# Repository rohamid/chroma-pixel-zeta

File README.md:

# TODO #
* Using IS42S16160 which is actually 32MB SDRAM, there must be 13 bit address (A0-A12). But I only populated 12-bit (A0-A11). Fix This
* Move the LCD FPC 40P slightly inside the PCB in order to match the actual LCD bend.
* Add VBUS control to the USB C in order to use USB Host capability
* I forgot to route 5V to 4P the JST-XH connector
* Rotate the ST-Link connector 180 degree to match the actual ST-Link connector bend

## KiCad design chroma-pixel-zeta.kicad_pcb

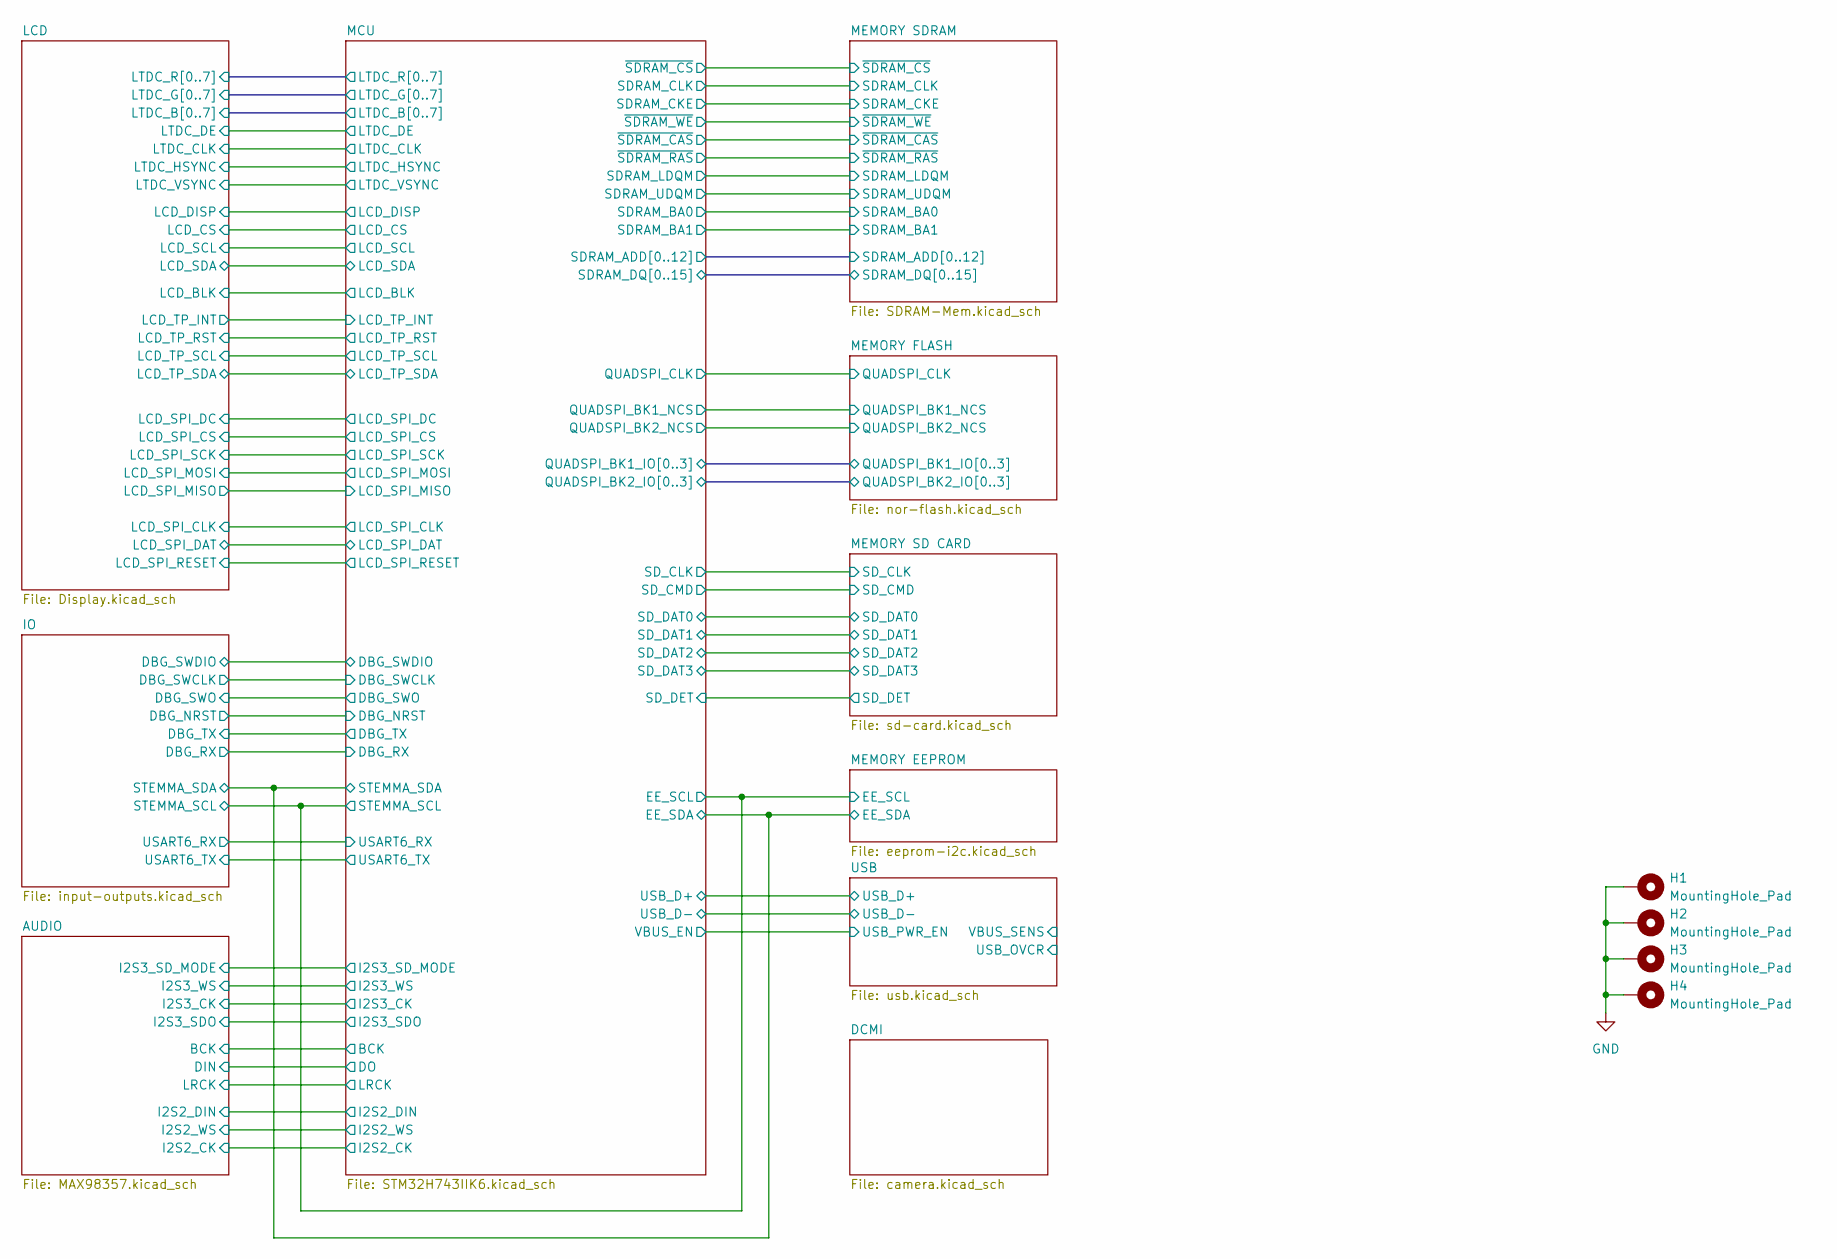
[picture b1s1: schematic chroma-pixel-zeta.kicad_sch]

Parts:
H1, H2, H3, H4: MountingHole_Pad; MountingHole_3.2mm_M3_Pad_Via

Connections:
GND: H1.1, H2.1, H3.1, H4.1; also elsewhere on the board

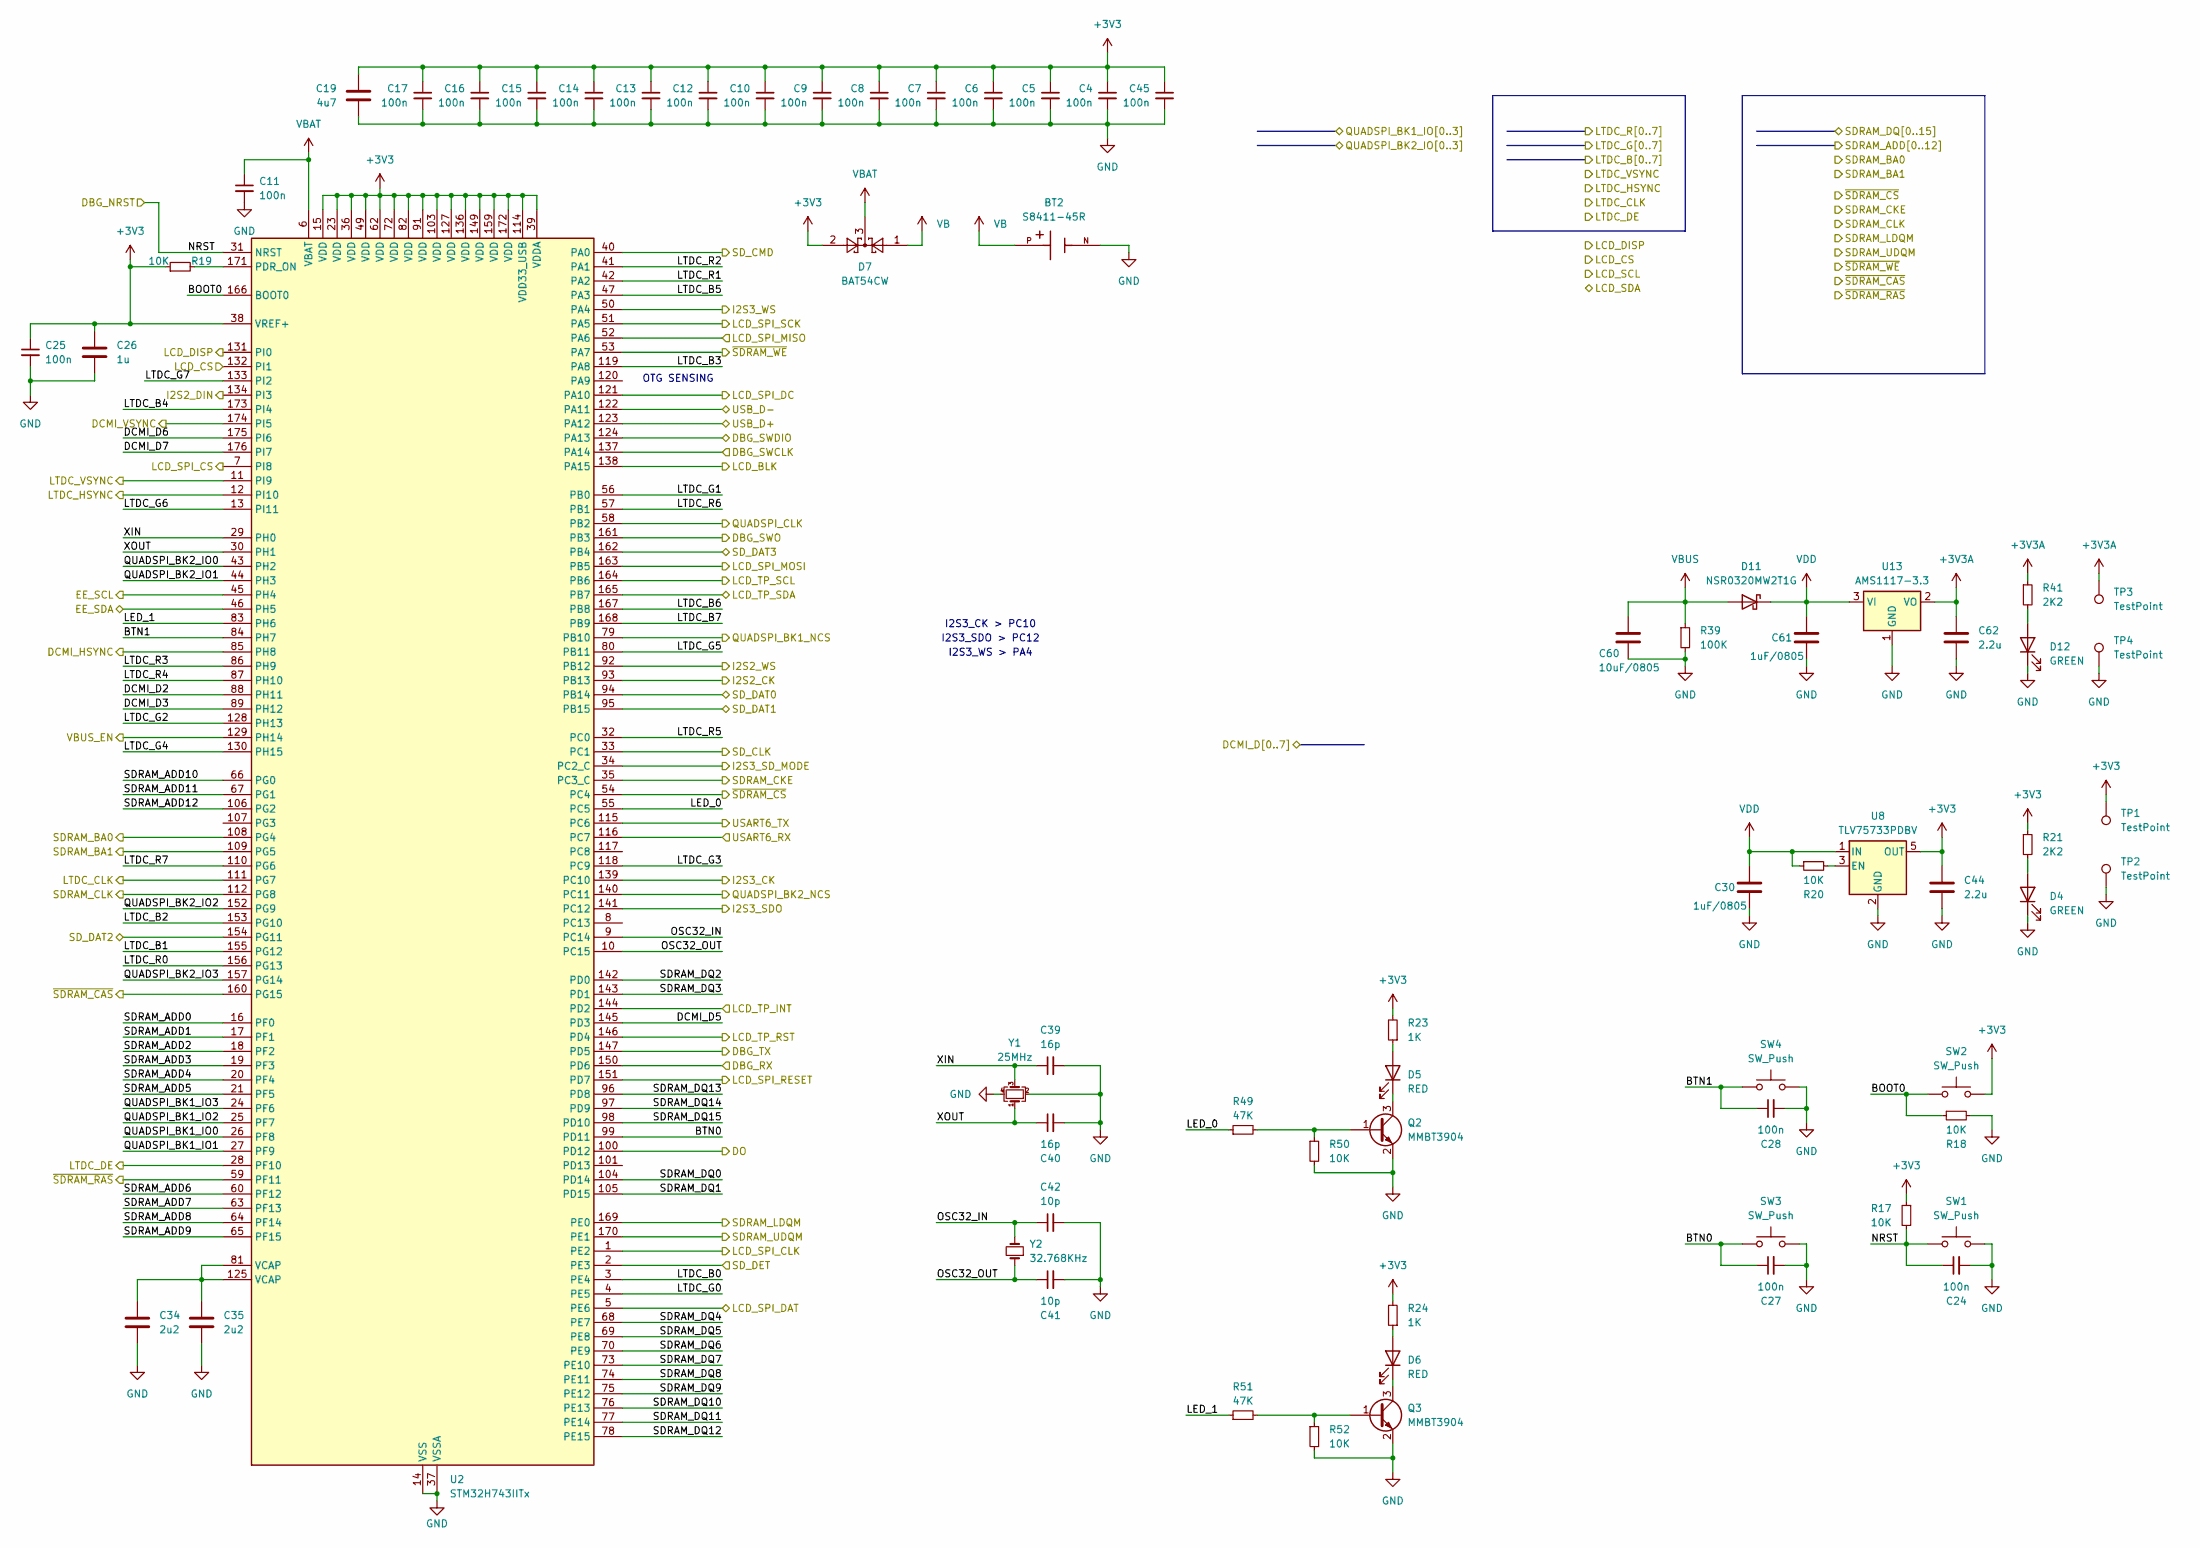
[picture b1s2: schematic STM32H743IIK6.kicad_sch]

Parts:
BT2: S8411-45R; CR1220-Batt-conn-S8411-45R; JLCPCB Part # C964729
C4, C5, C6, C7, C8, C9, C10, C11, C12, C13, C14, C15, C16, C17, C24, C25, C27, C28, C45: 100n; C_0402_1005Metric; JLCPCB Part # C307331
C19: 4u7; C_0603_1608Metric; JLCPCB Part # C19666
C26: 1u; C_0603_1608Metric; JLCPCB Part # C15849
C30, C61: 1uF/0805; C_0805_2012Metric; JLCPCB Part # C28323
C34, C35: 2u2; C_0603_1608Metric; JLCPCB Part # C23630
C39, C40: 16p; C_0402_1005Metric; JLCPCB Part # C77590
C41, C42: 10p; C_0402_1005Metric; JLCPCB Part # C32949
C44, C62: 2.2u; C_0805_2012Metric; JLCPCB Part # C377773
C60: 10uF/0805; C_0805_2012Metric; JLCPCB Part # C440198
D4, D12: GREEN; LED_0805_2012Metric; JLCPCB Part # C2297
D5, D6: RED; LED_0805_2012Metric; JLCPCB Part # C84256
D7: BAT54CW; SOT-23; JLCPCB Part # C37704
D11: NSR0320MW2T1G; D_SOD-323; JLCPCB Part # C48192
Q2, Q3: MMBT3904; SOT-23; JLCPCB Part # C20526
R17, R18, R19, R20, R50, R52: 10K; R_0402_1005Metric; JLCPCB Part # C25744
R21, R41: 2K2; R_0402_1005Metric; JLCPCB Part # C25879
R23, R24: 1K; R_0402_1005Metric; JLCPCB Part # C11702
R39: 100K; R_0402_1005Metric; JLCPCB Part # C60491
R49, R51: 47K; R_0402_1005Metric; JLCPCB Part # C25741
SW1, SW2, SW3, SW4: SW_Push; SW_SPST_PTS810; JLCPCB Part # C127488
TP1, TP2, TP3, TP4: TestPoint; TestPoint_Pad_D1.5mm
U2: STM32H743IITx; LQFP-176_24x24mm_P0.5mm; JLCPCB Part # C89597
U8: TLV75733PDBV; SOT-23-5; JLCPCB Part # C485517
U13: AMS1117-3.3; SOT-223-3_TabPin2; JLCPCB Part # C6186
Y1: 25MHz; Crystal_SMD_2520-4Pin_2.5x2.0mm; JLCPCB Part # C255954
Y2: 32.768KHz; Crystal_SMD_2012-2Pin_2.0x1.2mm; JLCPCB Part # C99009

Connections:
+3V3: C4.1, C5.1, C6.1, C7.1, C8.1, C9.1, C10.1, C12.1, C13.1, C14.1, C15.1, C16.1, C17.1, C19.1, C25.1, C26.1, C44.1, C45.1, D7.2, R17.1, R19.1, R21.1, R23.2, R24.2, SW2.2, TP1.1, U2.15 (VDD), U2.23 (VDD), U2.36 (VDD), U2.38 (VREF+), U2.39 (VDDA), U2.49 (VDD), U2.62 (VDD), U2.72 (VDD), U2.82 (VDD), U2.91 (VDD), U2.103 (VDD), U2.114 (VDD33_USB), U2.127 (VDD), U2.136 (VDD), U2.149 (VDD), U2.159 (VDD), U2.172 (VDD), U8.5 (OUT); also elsewhere on the board
+3V3A: C62.1, R41.1, TP3.1, U13.2 (VO); also elsewhere on the board
/AUDIO/I2S2_CK: U2.93 (PB13); also elsewhere on the board
/AUDIO/I2S2_DIN: U2.134 (PI3); also elsewhere on the board
/AUDIO/I2S2_WS: U2.92 (PB12); also elsewhere on the board
/AUDIO/I2S3_CK: U2.139 (PC10); also elsewhere on the board
/AUDIO/I2S3_SDO: U2.141 (PC12); also elsewhere on the board
/AUDIO/I2S3_SD_MODE: U2.34 (PC2_C); also elsewhere on the board
/AUDIO/I2S3_WS: U2.50 (PA4); also elsewhere on the board
/IO/DBG_RX: U2.150 (PD6); also elsewhere on the board
/IO/DBG_SWCLK: U2.137 (PA14); also elsewhere on the board
/IO/DBG_SWDIO: U2.124 (PA13); also elsewhere on the board
/IO/DBG_SWO: U2.161 (PB3); also elsewhere on the board
/IO/DBG_TX: U2.147 (PD5); also elsewhere on the board
/IO/STEMMA_SCL: U2.45 (PH4); also elsewhere on the board
/IO/STEMMA_SDA: U2.46 (PH5); also elsewhere on the board
/IO/USART6_RX: U2.116 (PC7); also elsewhere on the board
/IO/USART6_TX: U2.115 (PC6); also elsewhere on the board
/LCD/LCD_BLK: U2.138 (PA15); also elsewhere on the board
/LCD/LCD_CS: U2.132 (PI1); also elsewhere on the board
/LCD/LCD_DC: U2.121 (PA10); also elsewhere on the board
/LCD/LCD_DISP: U2.131 (PI0); also elsewhere on the board
/LCD/LCD_SCK: U2.51 (PA5); also elsewhere on the board
/LCD/LCD_SDI(MOSI): U2.163 (PB5); also elsewhere on the board
/LCD/LCD_SDO(MISO): U2.52 (PA6); also elsewhere on the board
/LCD/LCD_SPI_CLK: U2.1 (PE2); also elsewhere on the board
/LCD/LCD_SPI_CS: U2.7 (PI8); also elsewhere on the board
/LCD/LCD_SPI_DAT: U2.5 (PE6); also elsewhere on the board
/LCD/LCD_SPI_RESET: U2.151 (PD7); also elsewhere on the board
/LCD/LCD_TP_INT: U2.144 (PD2); also elsewhere on the board
/LCD/LCD_TP_RST: U2.146 (PD4); also elsewhere on the board
/LCD/LCD_TP_SCL: U2.164 (PB6); also elsewhere on the board
/LCD/LCD_TP_SDA: U2.165 (PB7); also elsewhere on the board
/LCD/LTDC_B0: U2.3 (PE4); also elsewhere on the board
/LCD/LTDC_B1: U2.155 (PG12); also elsewhere on the board
/LCD/LTDC_B2: U2.153 (PG10); also elsewhere on the board
/LCD/LTDC_B3: U2.119 (PA8); also elsewhere on the board
/LCD/LTDC_B4: U2.173 (PI4); also elsewhere on the board
/LCD/LTDC_B5: U2.47 (PA3); also elsewhere on the board
/LCD/LTDC_B6: U2.167 (PB8); also elsewhere on the board
/LCD/LTDC_B7: U2.168 (PB9); also elsewhere on the board
/LCD/LTDC_CLK: U2.111 (PG7); also elsewhere on the board
/LCD/LTDC_DE: U2.28 (PF10); also elsewhere on the board
/LCD/LTDC_G0: U2.4 (PE5); also elsewhere on the board
/LCD/LTDC_G1: U2.56 (PB0); also elsewhere on the board
/LCD/LTDC_G2: U2.128 (PH13); also elsewhere on the board
/LCD/LTDC_G3: U2.118 (PC9); also elsewhere on the board
/LCD/LTDC_G4: U2.130 (PH15); also elsewhere on the board
/LCD/LTDC_G5: U2.80 (PB11); also elsewhere on the board
/LCD/LTDC_G6: U2.13 (PI11); also elsewhere on the board
/LCD/LTDC_G7: U2.133 (PI2); also elsewhere on the board
/LCD/LTDC_HSYNC: U2.12 (PI10); also elsewhere on the board
/LCD/LTDC_R0: U2.156 (PG13); also elsewhere on the board
/LCD/LTDC_R1: U2.42 (PA2); also elsewhere on the board
/LCD/LTDC_R2: U2.41 (PA1); also elsewhere on the board
/LCD/LTDC_R3: U2.86 (PH9); also elsewhere on the board
/LCD/LTDC_R4: U2.87 (PH10); also elsewhere on the board
/LCD/LTDC_R5: U2.32 (PC0); also elsewhere on the board
/LCD/LTDC_R6: U2.57 (PB1); also elsewhere on the board
/LCD/LTDC_R7: U2.110 (PG6); also elsewhere on the board
/LCD/LTDC_VSYNC: U2.11 (PI9); also elsewhere on the board
/MCU/BOOT0: R18.1, SW2.1, U2.166 (BOOT0)
/MCU/BTN0: C27.1, SW3.1, U2.99 (PD11)
/MCU/BTN1: C28.1, SW4.1, U2.84 (PH7)
/MCU/DCMI_D2: U2.88 (PH11)
/MCU/DCMI_D3: U2.89 (PH12)
/MCU/DCMI_D5: U2.145 (PD3)
/MCU/DCMI_D6: U2.175 (PI6)
/MCU/DCMI_D7: U2.176 (PI7)
/MCU/DCMI_HSYNC: U2.85 (PH8)
/MCU/DCMI_VSYNC: U2.174 (PI5)
/MCU/DO: U2.100 (PD12)
/MCU/LED_0: R49.1, U2.55 (PC5)
/MCU/LED_1: R51.1, U2.83 (PH6)
/MCU/NRST: C24.1, R17.2, SW1.1, U2.31 (NRST); also elsewhere on the board
/MCU/OSC32_IN: C42.1, U2.9 (PC14), Y2.2
/MCU/OSC32_OUT: C41.1, U2.10 (PC15), Y2.1
/MCU/QUADSPI_BK1_IO0: U2.26 (PF8); also elsewhere on the board
/MCU/QUADSPI_BK1_IO1: U2.27 (PF9); also elsewhere on the board
/MCU/QUADSPI_BK1_IO2: U2.25 (PF7); also elsewhere on the board
/MCU/QUADSPI_BK1_IO3: U2.24 (PF6); also elsewhere on the board
/MCU/QUADSPI_BK1_NCS: U2.79 (PB10); also elsewhere on the board
/MCU/QUADSPI_BK2_IO0: U2.43 (PH2); also elsewhere on the board
/MCU/QUADSPI_BK2_IO1: U2.44 (PH3); also elsewhere on the board
/MCU/QUADSPI_BK2_IO2: U2.152 (PG9); also elsewhere on the board
/MCU/QUADSPI_BK2_IO3: U2.157 (PG14); also elsewhere on the board
/MCU/QUADSPI_BK2_NCS: U2.140 (PC11); also elsewhere on the board
/MCU/QUADSPI_CLK: U2.58 (PB2); also elsewhere on the board
/MCU/SDRAM_ADD0: U2.16 (PF0); also elsewhere on the board
/MCU/SDRAM_ADD1: U2.17 (PF1); also elsewhere on the board
/MCU/SDRAM_ADD2: U2.18 (PF2); also elsewhere on the board
/MCU/SDRAM_ADD3: U2.19 (PF3); also elsewhere on the board
/MCU/SDRAM_ADD4: U2.20 (PF4); also elsewhere on the board
/MCU/SDRAM_ADD5: U2.21 (PF5); also elsewhere on the board
/MCU/SDRAM_ADD6: U2.60 (PF12); also elsewhere on the board
/MCU/SDRAM_ADD7: U2.63 (PF13); also elsewhere on the board
/MCU/SDRAM_ADD8: U2.64 (PF14); also elsewhere on the board
/MCU/SDRAM_ADD9: U2.65 (PF15); also elsewhere on the board
/MCU/SDRAM_ADD10: U2.66 (PG0); also elsewhere on the board
/MCU/SDRAM_ADD11: U2.67 (PG1); also elsewhere on the board
/MCU/SDRAM_ADD12: U2.106 (PG2); also elsewhere on the board
/MCU/SDRAM_DQ0: U2.104 (PD14); also elsewhere on the board
/MCU/SDRAM_DQ1: U2.105 (PD15); also elsewhere on the board
/MCU/SDRAM_DQ2: U2.142 (PD0); also elsewhere on the board
/MCU/SDRAM_DQ3: U2.143 (PD1); also elsewhere on the board
/MCU/SDRAM_DQ4: U2.68 (PE7); also elsewhere on the board
/MCU/SDRAM_DQ5: U2.69 (PE8); also elsewhere on the board
/MCU/SDRAM_DQ6: U2.70 (PE9); also elsewhere on the board
/MCU/SDRAM_DQ7: U2.73 (PE10); also elsewhere on the board
/MCU/SDRAM_DQ8: U2.74 (PE11); also elsewhere on the board
/MCU/SDRAM_DQ9: U2.75 (PE12); also elsewhere on the board
/MCU/SDRAM_DQ10: U2.76 (PE13); also elsewhere on the board
/MCU/SDRAM_DQ11: U2.77 (PE14); also elsewhere on the board
/MCU/SDRAM_DQ12: U2.78 (PE15); also elsewhere on the board
/MCU/SDRAM_DQ13: U2.96 (PD8); also elsewhere on the board
/MCU/SDRAM_DQ14: U2.97 (PD9); also elsewhere on the board
/MCU/SDRAM_DQ15: U2.98 (PD10); also elsewhere on the board
/MCU/SD_CLK: U2.33 (PC1); also elsewhere on the board
/MCU/SD_CMD: U2.40 (PA0); also elsewhere on the board
/MCU/SD_DAT0: U2.94 (PB14); also elsewhere on the board
/MCU/SD_DAT1: U2.95 (PB15); also elsewhere on the board
/MCU/SD_DAT2: U2.154 (PG11); also elsewhere on the board
/MCU/SD_DAT3: U2.162 (PB4); also elsewhere on the board
/MCU/SD_DET: U2.2 (PE3); also elsewhere on the board
/MCU/VBUS_EN: U2.129 (PH14); also elsewhere on the board
/MCU/XIN: C39.1, U2.29 (PH0), Y1.3
/MCU/XOUT: C40.1, U2.30 (PH1), Y1.1
/MEMORY SDRAM/SDRAM_BA0: U2.108 (PG4); also elsewhere on the board
/MEMORY SDRAM/SDRAM_BA1: U2.109 (PG5); also elsewhere on the board
/MEMORY SDRAM/SDRAM_CKE: U2.35 (PC3_C); also elsewhere on the board
/MEMORY SDRAM/SDRAM_CLK: U2.112 (PG8); also elsewhere on the board
/MEMORY SDRAM/SDRAM_LDQM: U2.169 (PE0); also elsewhere on the board
/MEMORY SDRAM/SDRAM_UDQM: U2.170 (PE1); also elsewhere on the board
/MEMORY SDRAM/~SDRAM_CAS: U2.160 (PG15); also elsewhere on the board
/MEMORY SDRAM/~SDRAM_CS: U2.54 (PC4); also elsewhere on the board
/MEMORY SDRAM/~SDRAM_RAS: U2.59 (PF11); also elsewhere on the board
/MEMORY SDRAM/~SDRAM_WE: U2.53 (PA7); also elsewhere on the board
/USB/USB_D+: U2.123 (PA12); also elsewhere on the board
/USB/USB_D-: U2.122 (PA11); also elsewhere on the board
GND: BT2.N, C4.2, C5.2, C6.2, C7.2, C8.2, C9.2, C10.2, C11.2, C12.2, C13.2, C14.2, C15.2, C16.2, C17.2, C19.2, C24.2, C25.2, C26.2, C27.2, C28.2, C30.2, C34.2, C35.2, C39.2, C40.2, C41.2, C42.2, C44.2, C45.2, C60.2, C61.2, C62.2, D4.1 (K), D12.1 (K), Q2.2 (E), Q3.2 (E), R18.2, R39.2, R50.2, R52.2, SW1.2, SW3.2, SW4.2, TP2.1, TP4.1, U2.14 (VSS), U2.22 (VSS), U2.37 (VSSA), U2.48 (VSS), U2.61 (VSS), U2.71 (VSS), U2.90 (VSS), U2.102 (VSS), U2.113 (VSS), U2.126 (VSS), U2.135 (VSS), U2.148 (VSS), U2.158 (VSS), U8.2 (GND), U13.1 (GND), Y1.2, Y1.4; also elsewhere on the board
unnamed: C34.1, C35.1, U2.81 (VCAP), U2.125 (VCAP)
unnamed: D4.2 (A), R21.2
unnamed: D5.2 (A), R23.1
unnamed: D5.1 (K), Q2.3 (C)
unnamed: D6.2 (A), R24.1
unnamed: D6.1 (K), Q3.3 (C)
unnamed: D12.2 (A), R41.2
unnamed: Q2.1 (B), R49.2, R50.1
unnamed: Q3.1 (B), R51.2, R52.1
unnamed: R19.2, U2.171 (PDR_ON)
unnamed: R20.2, U8.3 (EN)
VB: BT2.P, D7.1
VBAT: C11.1, D7.3, U2.6 (VBAT)
VBUS: C60.1, D11.2 (A), R39.1; also elsewhere on the board
VDD: C30.1, C61.1, D11.1 (K), R20.1, U8.1 (IN), U13.3 (VI); also elsewhere on the board

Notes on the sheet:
I2S3_WS > PA4
I2S3_SDO > PC12
I2S3_CK > PC10
OTG SENSING

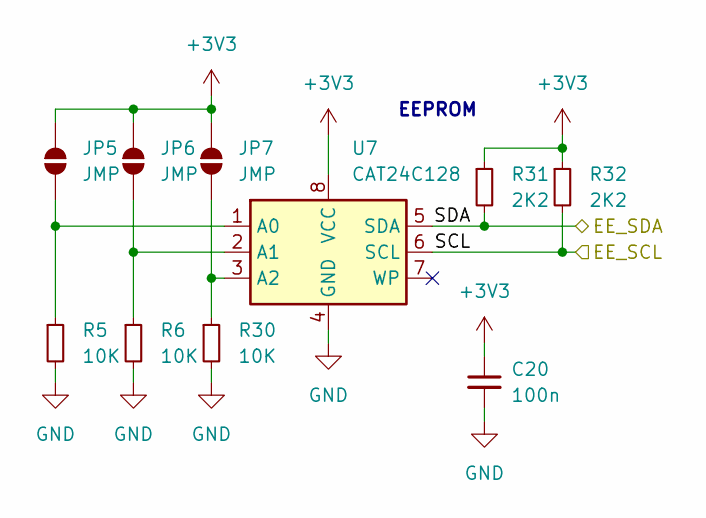
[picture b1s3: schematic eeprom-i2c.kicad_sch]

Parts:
C20: 100n; C_0402_1005Metric; JLCPCB Part # C307331
JP5, JP6, JP7: JMP; SolderJumper-2_P1.3mm_Open_RoundedPad1.0x1.5mm
R5, R6, R30: 10K; R_0402_1005Metric; JLCPCB Part # C25744
R31, R32: 2K2; R_0402_1005Metric; JLCPCB Part # C25879
U7: CAT24C128; SOIC-8_3.9x4.9mm_P1.27mm; JLCPCB Part # C6482

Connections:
+3V3: C20.1, JP5.2 (B), JP6.2 (B), JP7.2 (B), R31.1, R32.1, U7.8 (VCC); also elsewhere on the board
/IO/STEMMA_SCL: R32.2, U7.6 (SCL); also elsewhere on the board
/IO/STEMMA_SDA: R31.2, U7.5 (SDA); also elsewhere on the board
GND: C20.2, R5.2, R6.2, R30.2, U7.4 (GND); also elsewhere on the board
unnamed: JP5.1 (A), R5.1, U7.1 (A0)
unnamed: JP6.1 (A), R6.1, U7.2 (A1)
unnamed: JP7.1 (A), R30.1, U7.3 (A2)

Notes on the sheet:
EEPROM

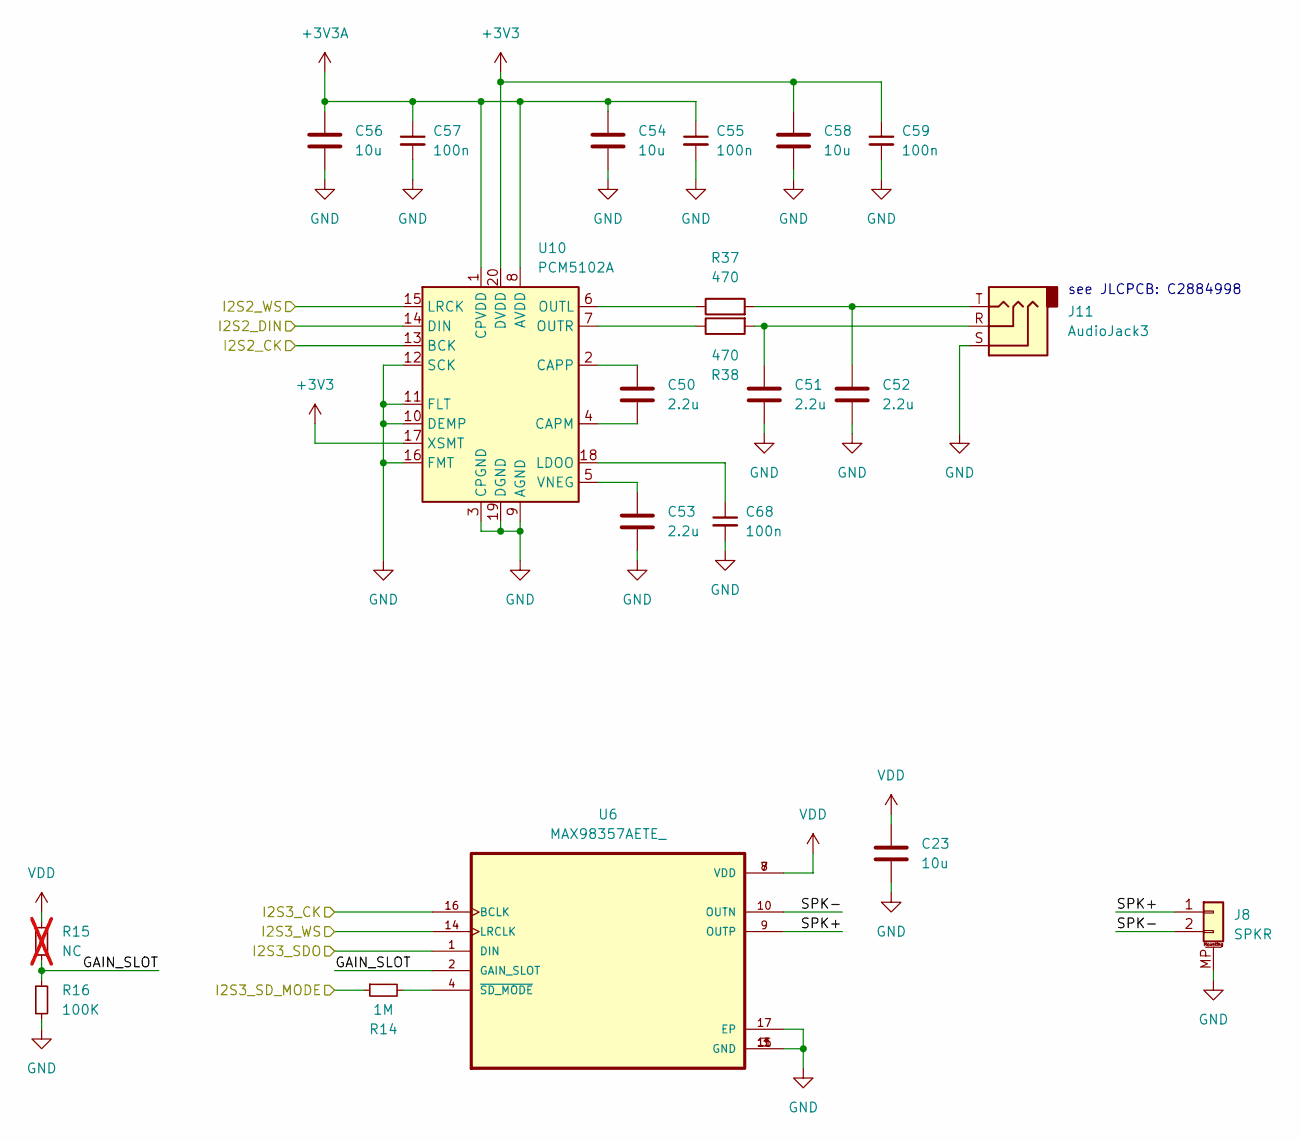
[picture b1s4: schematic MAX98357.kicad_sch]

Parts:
C23, C54, C56, C58: 10u; C_0603_1608Metric; JLCPCB Part # C96446
C50, C51, C52, C53: 2.2u; C_0805_2012Metric; JLCPCB Part # C377773
C55, C57, C59, C68: 100n; C_0402_1005Metric; JLCPCB Part # C307331
J8: SPKR; Hirose_DF13C_CL535-0402-2-51_1x02-1MP_P1.25mm_Vertical; JLCPCB Part # C7419891
J11: AudioJack3; XKB-PJ-320B-SMT; JLCPCB Part # C2884998
R14: 1M; R_0402_1005Metric; JLCPCB Part # C26083
R15: NC; R_0402_1005Metric; not fitted
R16: 100K; R_0402_1005Metric; JLCPCB Part # C60491
R37, R38: 470; R_0603_1608Metric; JLCPCB Part # C23179
U6: MAX98357AETE_; QFN50P300X300X80-17N; JLCPCB Part # C910544
U10: PCM5102A; TSSOP-20_4.4x6.5mm_P0.65mm; JLCPCB Part # C107671

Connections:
+3V3: C58.1, C59.1, U10.17 (XSMT), U10.20 (DVDD); also elsewhere on the board
+3V3A: C54.1, C55.1, C56.1, C57.1, U10.1 (CPVDD), U10.8 (AVDD); also elsewhere on the board
/AUDIO/GAIN_SLOT: R15.2, R16.1, U6.2 (GAIN_SLOT)
/AUDIO/I2S2_CK: U10.13 (BCK); also elsewhere on the board
/AUDIO/I2S2_DIN: U10.14 (DIN); also elsewhere on the board
/AUDIO/I2S2_WS: U10.15 (LRCK); also elsewhere on the board
/AUDIO/I2S3_CK: U6.16 (BCLK); also elsewhere on the board
/AUDIO/I2S3_SDO: U6.1 (DIN); also elsewhere on the board
/AUDIO/I2S3_SD_MODE: R14.1; also elsewhere on the board
/AUDIO/I2S3_WS: U6.14 (LRCLK); also elsewhere on the board
/AUDIO/SPK+: J8.1, U6.9 (OUTP)
/AUDIO/SPK-: J8.2, U6.10 (OUTN)
GND: C23.2, C51.2, C52.2, C53.2, C54.2, C55.2, C56.2, C57.2, C58.2, C59.2, C68.2, J8.MP (MountPin), J11.S, R16.2, U6.3 (GND), U6.11 (GND), U6.15 (GND), U6.17 (EP), U10.3 (CPGND), U10.9 (AGND), U10.10 (DEMP), U10.11 (FLT), U10.12 (SCK), U10.16 (FMT), U10.19 (DGND); also elsewhere on the board
unnamed: C51.1, J11.R, R38.2
unnamed: C52.1, J11.T, R37.2
unnamed: R14.2, U6.4 (~SD_MODE)
unnamed: C50.2, U10.4 (CAPM)
unnamed: C50.1, U10.2 (CAPP)
unnamed: C68.1, U10.18 (LDOO)
unnamed: R37.1, U10.6 (OUTL)
unnamed: R38.1, U10.7 (OUTR)
unnamed: C53.1, U10.5 (VNEG)
VDD: C23.1, R15.1, U6.7 (VDD), U6.8 (VDD); also elsewhere on the board

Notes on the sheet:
see JLCPCB: C2884998

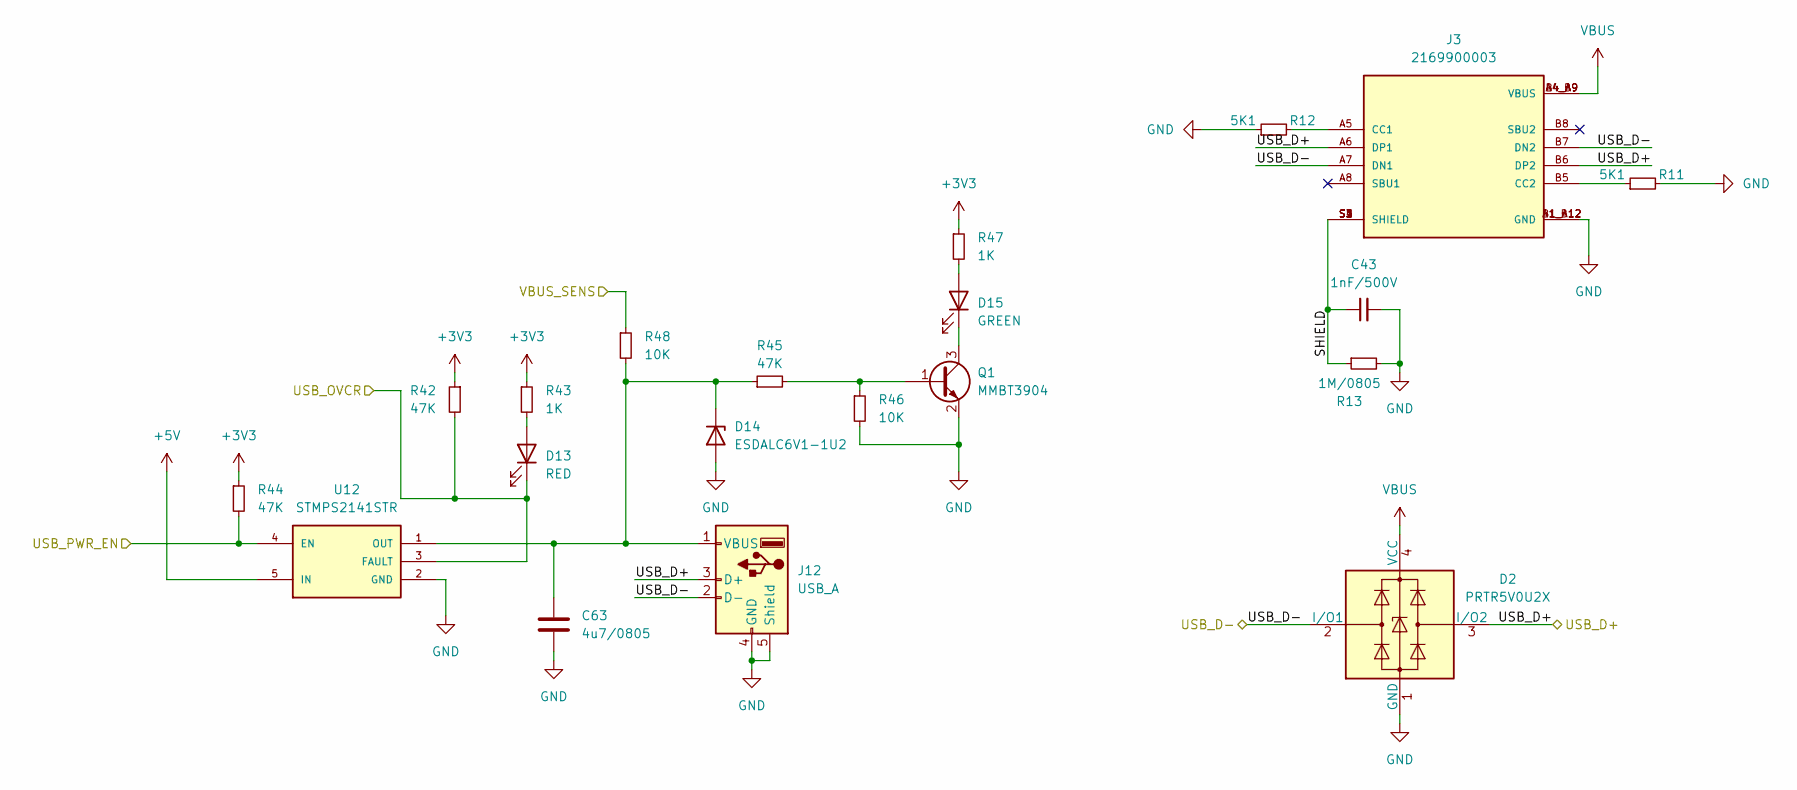
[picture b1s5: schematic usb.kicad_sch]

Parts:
C43: 1nF/500V; C_1206_3216Metric; JLCPCB Part # C35216
C63: 4u7/0805; C_0805_2012Metric; JLCPCB Part # C98192
D2: PRTR5V0U2X; SOT-143; JLCPCB Part # C12333
D13: RED; LED_0805_2012Metric; JLCPCB Part # C84256
D14: ESDALC6V1-1U2; D_SOD-523; JLCPCB Part # C1974498
D15: GREEN; LED_0805_2012Metric; JLCPCB Part # C2297
J3: 2169900003; USB_C_Mid_mount_MOLEX_2169900003; PARTREV A1
J12: USB_A; USB_A_Molex_67643_Horizontal
Q1: MMBT3904; SOT-23; JLCPCB Part # C20526
R11, R12: 5K1; R_0402_1005Metric; JLCPCB Part # C25905
R13: 1M/0805; R_0805_2012Metric; JLCPCB Part # C17514
R42, R44, R45: 47K; R_0402_1005Metric; JLCPCB Part # C25741
R43, R47: 1K; R_0402_1005Metric; JLCPCB Part # C11702
R46, R48: 10K; R_0402_1005Metric; JLCPCB Part # C25744
U12: STMPS2141STR; SOT95P280X145-5N; JLCPCB Part # C54624

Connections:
+3V3: R42.1, R43.1, R44.1, R47.1; also elsewhere on the board
+5V: U12.5 (IN); also elsewhere on the board
/MCU/VBUS_EN: R44.2, U12.4 (EN); also elsewhere on the board
/USB/SHIELD: C43.1, J3.S1 (SHIELD), J3.S2 (SHIELD), J3.S3 (SHIELD), J3.S4 (SHIELD), R13.1
/USB/USB_D+: D2.3 (I/O2), J3.A6 (DP1), J3.B6 (DP2), J12.3 (D+); also elsewhere on the board
/USB/USB_D-: D2.2 (I/O1), J3.A7 (DN1), J3.B7 (DN2), J12.2 (D-); also elsewhere on the board
/USB/USB_OVCR: D13.1 (K), R42.2, U12.3 (FAULT)
/USB/VBUS_SENS: R48.1
GND: C43.2, C63.2, D2.1 (GND), D14.2 (A), J3.A1_B12 (GND), J3.B1_A12 (GND), J12.4 (GND), J12.5 (Shield), Q1.2 (E), R11.2, R12.1, R13.2, R46.2, U12.2 (GND); also elsewhere on the board
unnamed: D13.2 (A), R43.2
unnamed: C63.1, D14.1 (K), J12.1 (VBUS), R45.1, R48.2, U12.1 (OUT)
unnamed: D15.2 (A), R47.2
unnamed: D15.1 (K), Q1.3 (C)
unnamed: J3.A5 (CC1), R12.2
unnamed: J3.B5 (CC2), R11.1
unnamed: Q1.1 (B), R45.2, R46.1
VBUS: D2.4 (VCC), J3.A4_B9 (VBUS), J3.B4_A9 (VBUS); also elsewhere on the board

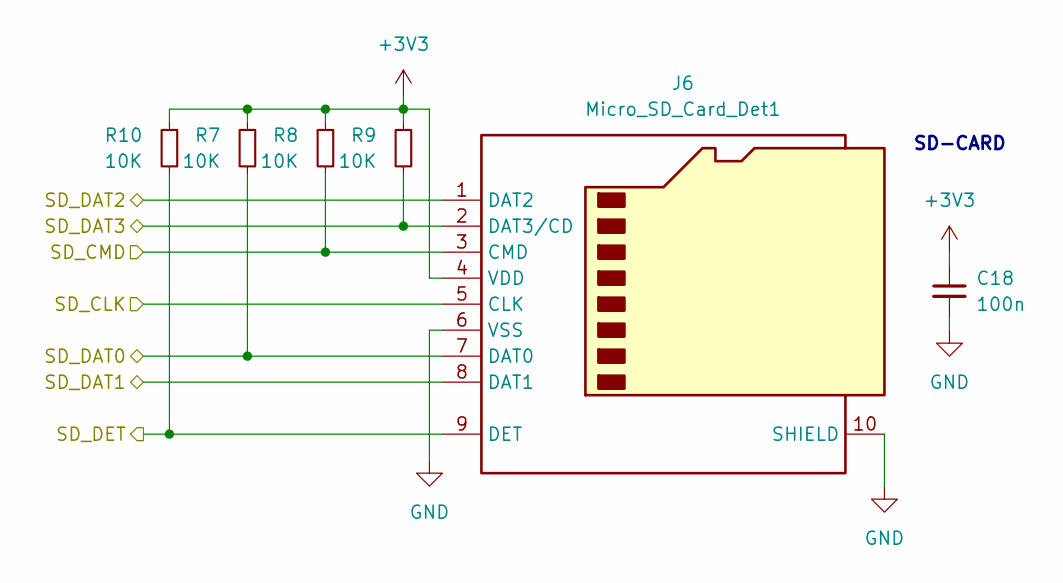
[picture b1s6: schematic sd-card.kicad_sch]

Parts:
C18: 100n; C_0402_1005Metric; JLCPCB Part # C307331
J6: Micro_SD_Card_Det1; SD-TF-115; JLCPCB Part # C266621
R7, R8, R9, R10: 10K; R_0402_1005Metric; JLCPCB Part # C25744

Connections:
+3V3: C18.1, J6.4 (VDD), R7.1, R8.1, R9.1, R10.1; also elsewhere on the board
/MCU/SD_CLK: J6.5 (CLK); also elsewhere on the board
/MCU/SD_CMD: J6.3 (CMD), R8.2; also elsewhere on the board
/MCU/SD_DAT0: J6.7 (DAT0), R7.2; also elsewhere on the board
/MCU/SD_DAT1: J6.8 (DAT1); also elsewhere on the board
/MCU/SD_DAT2: J6.1 (DAT2); also elsewhere on the board
/MCU/SD_DAT3: J6.2 (DAT3/CD), R9.2; also elsewhere on the board
/MCU/SD_DET: J6.9 (DET), R10.2; also elsewhere on the board
GND: C18.2, J6.6 (VSS), J6.10 (SHIELD); also elsewhere on the board

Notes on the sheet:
SD-CARD
